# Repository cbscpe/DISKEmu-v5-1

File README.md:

# DISK Emulator

## Introduction
The Q-BUS is a bus invented by DEC and was first used for small PDP-11 systems like the LSI-11. There were several backplanes available from DEC
and 3rd parties. For a complete PDP-11 system you needed a CPU card, memory, at least a console and some sort of mass storage device. Depending
on the operation sytem you needed additional cards like a line time clock and others.

## Controller Card
This is a Q-BUS PCB for a Q-BUS PDP-11 system that emulates disk controllers depending on the firmware of the microcontroller and the CPLD design files.
Currently there are two disk controller emulation, a RLV12 controller with four RL01/02 disks attached and a MSCP controller with four units.
The Q-BUS controller provides a command line interface to control the functions and configuration and a SD-Card to store the PDP-11 disk images.

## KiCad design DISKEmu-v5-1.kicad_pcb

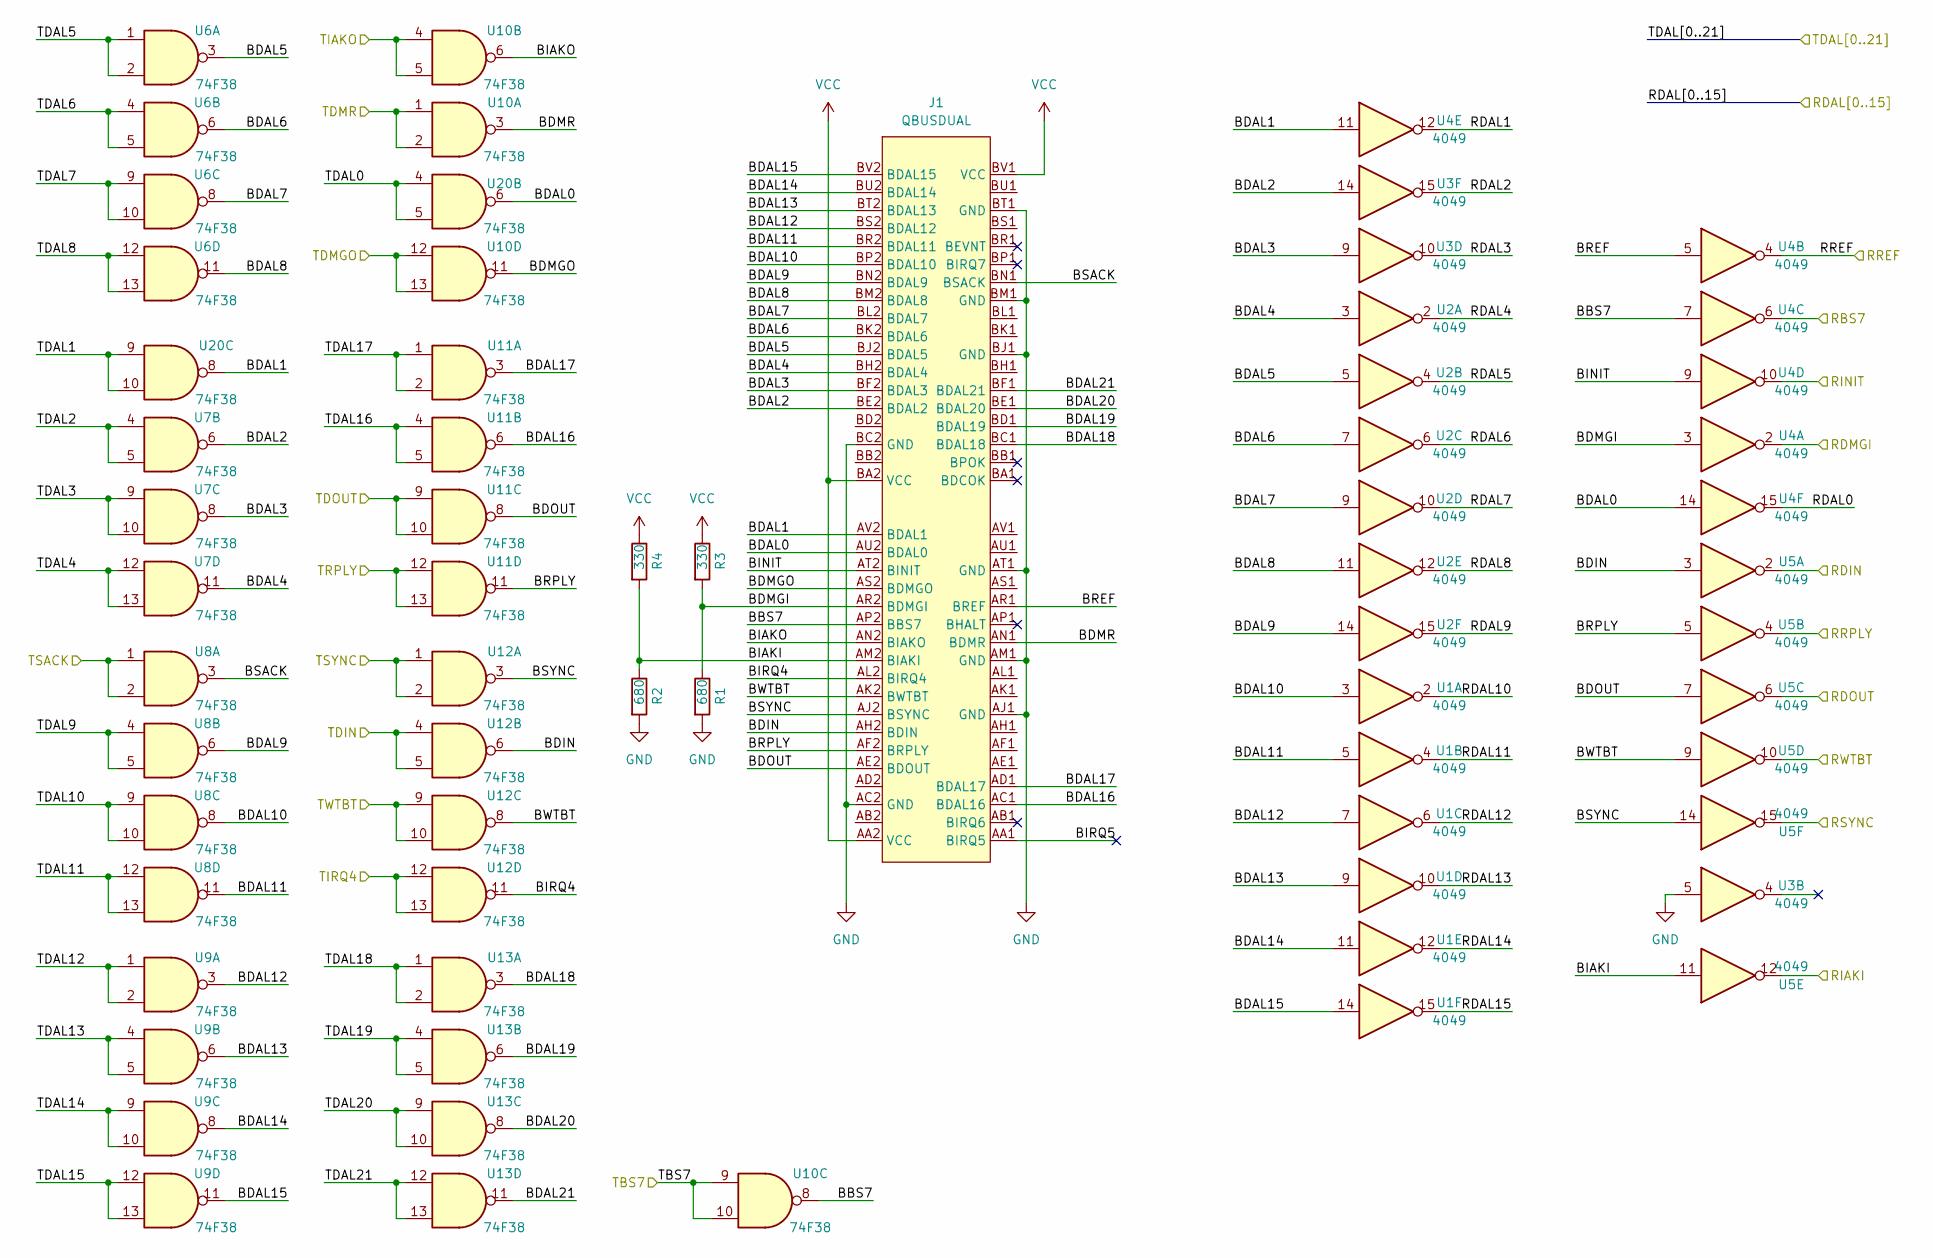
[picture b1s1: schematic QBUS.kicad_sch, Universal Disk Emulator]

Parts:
J1: QBUSDUAL; Q-Bus_Dual_Edge
R1, R2: 680; R_0603_1608Metric_Pad0.98x0.95mm_HandSolder
R3, R4: 330; R_0603_1608Metric_Pad0.98x0.95mm_HandSolder
U1, U2, U3, U4, U5: 4049; SOIC-16_3.9x9.9mm_P1.27mm
U6, U7, U8, U9, U10, U11, U12, U13, U20: 74F38; SOIC-14_3.9x8.7mm_P1.27mm

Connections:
/QBUS/BBS7: J1.AP2 (BBS7), U4.7, U10.8
/QBUS/BDAL0: J1.AU2 (BDAL0), U4.14, U20.6
/QBUS/BDAL1: J1.AV2 (BDAL1), U4.11, U20.8
/QBUS/BDAL2: J1.BE2 (BDAL2), U3.14, U7.6
/QBUS/BDAL3: J1.BF2 (BDAL3), U3.9, U7.8
/QBUS/BDAL4: J1.BH2 (BDAL4), U2.3, U7.11
/QBUS/BDAL5: J1.BJ2 (BDAL5), U2.5, U6.3
/QBUS/BDAL6: J1.BK2 (BDAL6), U2.7, U6.6
/QBUS/BDAL7: J1.BL2 (BDAL7), U2.9, U6.8
/QBUS/BDAL8: J1.BM2 (BDAL8), U2.11, U6.11
/QBUS/BDAL9: J1.BN2 (BDAL9), U2.14, U8.6
/QBUS/BDAL10: J1.BP2 (BDAL10), U1.3, U8.8
/QBUS/BDAL11: J1.BR2 (BDAL11), U1.5, U8.11
/QBUS/BDAL12: J1.BS2 (BDAL12), U1.7, U9.3
/QBUS/BDAL13: J1.BT2 (BDAL13), U1.9, U9.6
/QBUS/BDAL14: J1.BU2 (BDAL14), U1.11, U9.8
/QBUS/BDAL15: J1.BV2 (BDAL15), U1.14, U9.11
/QBUS/BDAL16: J1.AC1 (BDAL16), U11.6
/QBUS/BDAL17: J1.AD1 (BDAL17), U11.3
/QBUS/BDAL18: J1.BC1 (BDAL18), U13.3
/QBUS/BDAL19: J1.BD1 (BDAL19), U13.6
/QBUS/BDAL20: J1.BE1 (BDAL20), U13.8
/QBUS/BDAL21: J1.BF1 (BDAL21), U13.11
/QBUS/BDIN: J1.AH2 (BDIN), U5.3, U12.6
/QBUS/BDMGI: J1.AR2 (BDMGI), R1.1, R3.2, U4.3
/QBUS/BDMGO: J1.AS2 (BDMGO), U10.11
/QBUS/BDMR: J1.AN1 (BDMR), U10.3
/QBUS/BDOUT: J1.AE2 (BDOUT), U5.7, U11.8
/QBUS/BIAKI: J1.AM2 (BIAKI), R2.1, R4.2, U5.11
/QBUS/BIAKO: J1.AN2 (BIAKO), U10.6
/QBUS/BINIT: J1.AT2 (BINIT), U4.9
/QBUS/BIRQ4: J1.AL2 (BIRQ4), U12.11
/QBUS/BIRQ5: J1.AA1 (BIRQ5)
/QBUS/BREF: J1.AR1 (BREF), U4.5
/QBUS/BRPLY: J1.AF2 (BRPLY), U5.5, U11.11
/QBUS/BSACK: J1.BN1 (BSACK), U8.3
/QBUS/BSYNC: J1.AJ2 (BSYNC), U5.14, U12.3
/QBUS/BWTBT: J1.AK2 (BWTBT), U5.9, U12.8
/RBS7: U4.6; also elsewhere on the board
/RDAL0: U4.15; also elsewhere on the board
/RDAL1: U4.12; also elsewhere on the board
/RDAL2: U3.15; also elsewhere on the board
/RDAL3: U3.10; also elsewhere on the board
/RDAL4: U2.2; also elsewhere on the board
/RDAL5: U2.4; also elsewhere on the board
/RDAL6: U2.6; also elsewhere on the board
/RDAL7: U2.10; also elsewhere on the board
/RDAL8: U2.12; also elsewhere on the board
/RDAL9: U2.15; also elsewhere on the board
/RDAL10: U1.2; also elsewhere on the board
/RDAL11: U1.4; also elsewhere on the board
/RDAL12: U1.6; also elsewhere on the board
/RDAL13: U1.10; also elsewhere on the board
/RDAL14: U1.12; also elsewhere on the board
/RDAL15: U1.15; also elsewhere on the board
/RDIN: U5.2; also elsewhere on the board
/RDMIG: U4.2; also elsewhere on the board
/RDOUT: U5.6; also elsewhere on the board
/RIAKI: U5.12; also elsewhere on the board
/RINIT: U4.10; also elsewhere on the board
/RREF: U4.4; also elsewhere on the board
/RRPLY: U5.4; also elsewhere on the board
/RSYNC: U5.15; also elsewhere on the board
/RWTBT: U5.10; also elsewhere on the board
/TBS7: U10.9, U10.10; also elsewhere on the board
/TDAL0: U20.4, U20.5; also elsewhere on the board
/TDAL1: U20.9, U20.10; also elsewhere on the board
/TDAL2: U7.4, U7.5; also elsewhere on the board
/TDAL3: U7.9, U7.10; also elsewhere on the board
/TDAL4: U7.12, U7.13; also elsewhere on the board
/TDAL5: U6.1, U6.2; also elsewhere on the board
/TDAL6: U6.4, U6.5; also elsewhere on the board
/TDAL7: U6.9, U6.10; also elsewhere on the board
/TDAL8: U6.12, U6.13; also elsewhere on the board
/TDAL9: U8.4, U8.5; also elsewhere on the board
/TDAL10: U8.9, U8.10; also elsewhere on the board
/TDAL11: U8.12, U8.13; also elsewhere on the board
/TDAL12: U9.1, U9.2; also elsewhere on the board
/TDAL13: U9.4, U9.5; also elsewhere on the board
/TDAL14: U9.9, U9.10; also elsewhere on the board
/TDAL15: U9.12, U9.13; also elsewhere on the board
/TDAL16: U11.4, U11.5; also elsewhere on the board
/TDAL17: U11.1, U11.2; also elsewhere on the board
/TDAL18: U13.1, U13.2; also elsewhere on the board
/TDAL19: U13.4, U13.5; also elsewhere on the board
/TDAL20: U13.9, U13.10; also elsewhere on the board
/TDAL21: U13.12, U13.13; also elsewhere on the board
/TDIN: U12.4, U12.5; also elsewhere on the board
/TDMGO: U10.12, U10.13; also elsewhere on the board
/TDMR: U10.1, U10.2; also elsewhere on the board
/TDOUT: U11.9, U11.10; also elsewhere on the board
/TIAKO: U10.4, U10.5; also elsewhere on the board
/TIQR4: U12.12, U12.13; also elsewhere on the board
/TRPLY: U11.12, U11.13; also elsewhere on the board
/TSACK: U8.1, U8.2; also elsewhere on the board
/TSYNC: U12.1, U12.2; also elsewhere on the board
/TWTBT: U12.9, U12.10; also elsewhere on the board
GND: J1.AC2 (GND), J1.AJ1 (GND), J1.AM1 (GND), J1.AT1 (GND), J1.BC2 (GND), J1.BJ1 (GND), J1.BM1 (GND), J1.BT1 (GND), R1.2, R2.2, U3.5; also elsewhere on the board
VCC: J1.AA2 (VCC), J1.BA2 (VCC), J1.BV1 (VCC), R3.1, R4.1; also elsewhere on the board

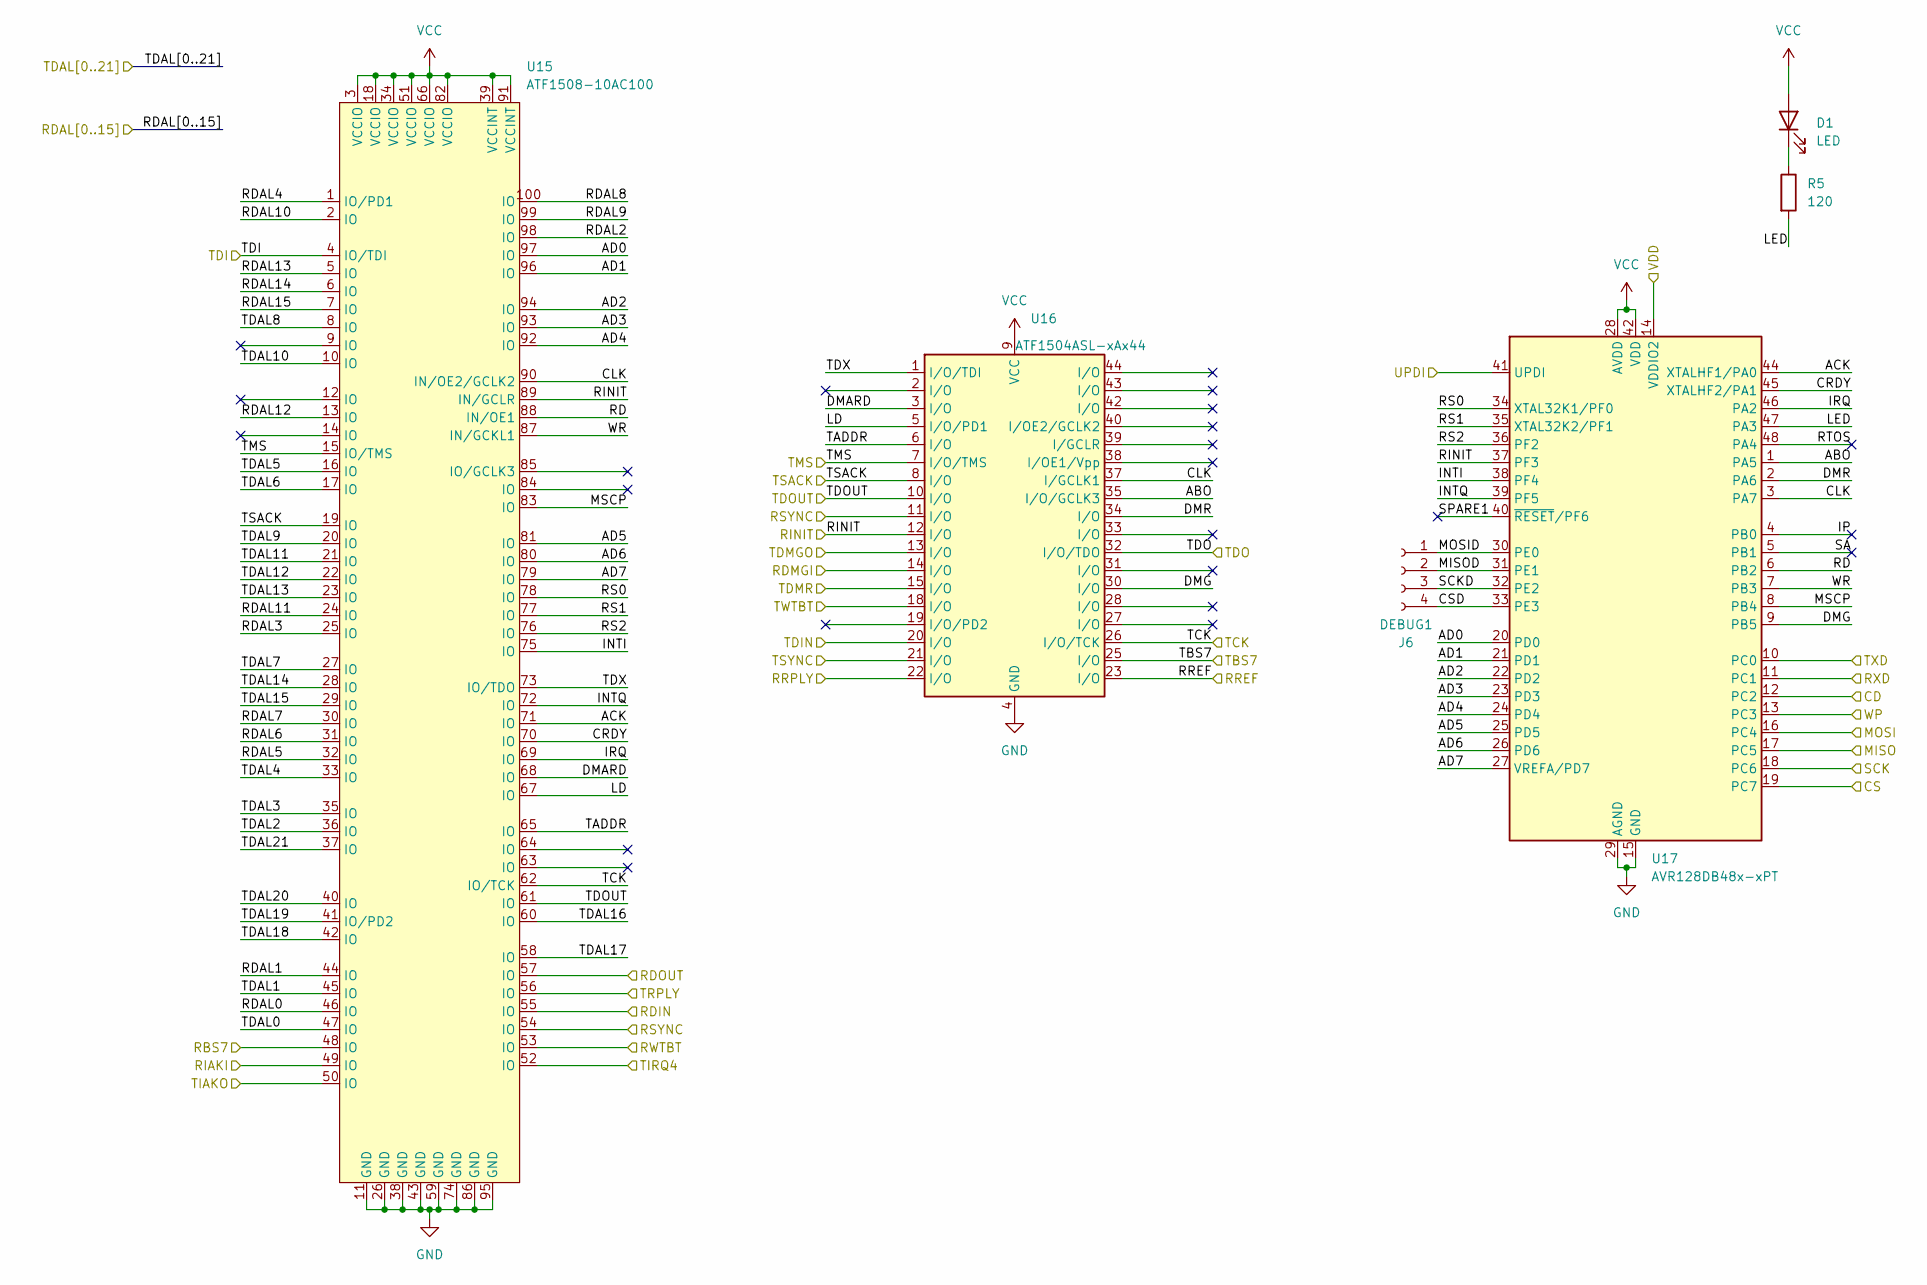
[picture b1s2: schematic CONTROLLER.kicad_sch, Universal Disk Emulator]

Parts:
D1: LED; LED_1206_3216Metric_Pad1.42x1.75mm_HandSolder
J6: DEBUG1; PinSocket_1x04_P2.54mm_Horizontal
R5: 120; R_0603_1608Metric_Pad0.98x0.95mm_HandSolder
U15: ATF1508-10AC100; TQFP-100_14x14mm_P0.5mm
U16: ATF1504ASL-xAx44; TQFP-44_10x10mm_P0.8mm
U17: AVR128DB48x-xPT; TQFP-48_7x7mm_P0.5mm

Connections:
/CD: U17.12 (PC2); also elsewhere on the board
/CONTROLLER/ABO: U16.35 (I/O/GCLK3), U17.1 (PA5)
/CONTROLLER/ACK: U15.71 (IO), U17.44 (XTALHF1/PA0)
/CONTROLLER/AD0: U15.97 (IO), U17.20 (PD0)
/CONTROLLER/AD1: U15.96 (IO), U17.21 (PD1)
/CONTROLLER/AD2: U15.94 (IO), U17.22 (PD2)
/CONTROLLER/AD3: U15.93 (IO), U17.23 (PD3)
/CONTROLLER/AD4: U15.92 (IO), U17.24 (PD4)
/CONTROLLER/AD5: U15.81 (IO), U17.25 (PD5)
/CONTROLLER/AD6: U15.80 (IO), U17.26 (PD6)
/CONTROLLER/AD7: U15.79 (IO), U17.27 (VREFA/PD7)
/CONTROLLER/CLK: U15.90 (IN/OE2/GCLK2), U16.37 (I/GCLK1), U17.3 (PA7)
/CONTROLLER/CRDY: U15.70 (IO), U17.45 (XTALHF2/PA1)
/CONTROLLER/CSD: J6.4, U17.33 (PE3)
/CONTROLLER/DMARD: U15.68 (IO), U16.3 (I/O)
/CONTROLLER/DMG: U16.30 (I/O), U17.9 (PB5)
/CONTROLLER/DMR: U16.34 (I/O), U17.2 (PA6)
/CONTROLLER/INTI: U15.75 (IO), U17.38 (PF4)
/CONTROLLER/INTQ: U15.72 (IO), U17.39 (PF5)
/CONTROLLER/IP: U17.4 (PB0)
/CONTROLLER/IRQ: U15.69 (IO), U17.46 (PA2)
/CONTROLLER/LD: U15.67 (IO), U16.5 (I/O/PD1)
/CONTROLLER/LED: R5.2, U17.47 (PA3)
/CONTROLLER/MISOD: J6.2, U17.31 (PE1)
/CONTROLLER/MOSID: J6.1, U17.30 (PE0)
/CONTROLLER/MSCP: U15.83 (IO), U17.8 (PB4)
/CONTROLLER/RD: U15.88 (IN/OE1), U17.6 (PB2)
/CONTROLLER/RS0: U15.78 (IO), U17.34 (XTAL32K1/PF0)
/CONTROLLER/RS1: U15.77 (IO), U17.35 (XTAL32K2/PF1)
/CONTROLLER/RS2: U15.76 (IO), U17.36 (PF2)
/CONTROLLER/RTOS: U17.48 (PA4)
/CONTROLLER/SA: U17.5 (PB1)
/CONTROLLER/SCKD: J6.3, U17.32 (PE2)
/CONTROLLER/SPARE1: U17.40 (~RESET/PF6)
/CONTROLLER/TADDR: U15.65 (IO), U16.6 (I/O)
/CONTROLLER/TDX: U15.73 (IO/TDO), U16.1 (I/O/TDI)
/CONTROLLER/WR: U15.87 (IN/GCKL1), U17.7 (PB3)
/CS: U17.19 (PC7); also elsewhere on the board
/MISO: U17.17 (PC5); also elsewhere on the board
/MOSI: U17.16 (PC4); also elsewhere on the board
/RBS7: U15.48 (IO); also elsewhere on the board
/RDAL0: U15.46 (IO); also elsewhere on the board
/RDAL1: U15.44 (IO); also elsewhere on the board
/RDAL2: U15.98 (IO); also elsewhere on the board
/RDAL3: U15.25 (IO); also elsewhere on the board
/RDAL4: U15.1 (IO/PD1); also elsewhere on the board
/RDAL5: U15.32 (IO); also elsewhere on the board
/RDAL6: U15.31 (IO); also elsewhere on the board
/RDAL7: U15.30 (IO); also elsewhere on the board
/RDAL8: U15.100 (IO); also elsewhere on the board
/RDAL9: U15.99 (IO); also elsewhere on the board
/RDAL10: U15.2 (IO); also elsewhere on the board
/RDAL11: U15.24 (IO); also elsewhere on the board
/RDAL12: U15.13 (IO); also elsewhere on the board
/RDAL13: U15.5 (IO); also elsewhere on the board
/RDAL14: U15.6 (IO); also elsewhere on the board
/RDAL15: U15.7 (IO); also elsewhere on the board
/RDIN: U15.55 (IO); also elsewhere on the board
/RDMIG: U16.14 (I/O); also elsewhere on the board
/RDOUT: U15.57 (IO); also elsewhere on the board
/RIAKI: U15.49 (IO); also elsewhere on the board
/RINIT: U15.89 (IN/GCLR), U16.12 (I/O), U17.37 (PF3); also elsewhere on the board
/RREF: U16.23 (I/O); also elsewhere on the board
/RRPLY: U16.22 (I/O); also elsewhere on the board
/RSYNC: U15.54 (IO), U16.11 (I/O); also elsewhere on the board
/RWTBT: U15.53 (IO); also elsewhere on the board
/RXD: U17.11 (PC1); also elsewhere on the board
/SCK: U17.18 (PC6); also elsewhere on the board
/TBS7: U16.25 (I/O); also elsewhere on the board
/TCK: U15.62 (IO/TCK), U16.26 (I/O/TCK); also elsewhere on the board
/TDAL0: U15.47 (IO); also elsewhere on the board
/TDAL1: U15.45 (IO); also elsewhere on the board
/TDAL2: U15.36 (IO); also elsewhere on the board
/TDAL3: U15.35 (IO); also elsewhere on the board
/TDAL4: U15.33 (IO); also elsewhere on the board
/TDAL5: U15.16 (IO); also elsewhere on the board
/TDAL6: U15.17 (IO); also elsewhere on the board
/TDAL7: U15.27 (IO); also elsewhere on the board
/TDAL8: U15.8 (IO); also elsewhere on the board
/TDAL9: U15.20 (IO); also elsewhere on the board
/TDAL10: U15.10 (IO); also elsewhere on the board
/TDAL11: U15.21 (IO); also elsewhere on the board
/TDAL12: U15.22 (IO); also elsewhere on the board
/TDAL13: U15.23 (IO); also elsewhere on the board
/TDAL14: U15.28 (IO); also elsewhere on the board
/TDAL15: U15.29 (IO); also elsewhere on the board
/TDAL16: U15.60 (IO); also elsewhere on the board
/TDAL17: U15.58 (IO); also elsewhere on the board
/TDAL18: U15.42 (IO); also elsewhere on the board
/TDAL19: U15.41 (IO/PD2); also elsewhere on the board
/TDAL20: U15.40 (IO); also elsewhere on the board
/TDAL21: U15.37 (IO); also elsewhere on the board
/TDI: U15.4 (IO/TDI); also elsewhere on the board
/TDIN: U16.20 (I/O); also elsewhere on the board
/TDMGO: U16.13 (I/O); also elsewhere on the board
/TDMR: U16.15 (I/O); also elsewhere on the board
/TDO: U16.32 (I/O/TDO); also elsewhere on the board
/TDOUT: U15.61 (IO), U16.10 (I/O); also elsewhere on the board
/TIAKO: U15.50 (IO); also elsewhere on the board
/TIQR4: U15.52 (IO); also elsewhere on the board
/TMS: U15.15 (IO/TMS), U16.7 (I/O/TMS); also elsewhere on the board
/TRPLY: U15.56 (IO); also elsewhere on the board
/TSACK: U15.19 (IO), U16.8 (I/O); also elsewhere on the board
/TSYNC: U16.21 (I/O); also elsewhere on the board
/TWTBT: U16.18 (I/O); also elsewhere on the board
/TXD: U17.10 (PC0); also elsewhere on the board
/UPDI: U17.41 (UPDI); also elsewhere on the board
/VDD: U17.14 (VDDIO2); also elsewhere on the board
/WP: U17.13 (PC3); also elsewhere on the board
GND: U15.11 (GND), U15.26 (GND), U15.38 (GND), U15.43 (GND), U15.59 (GND), U15.74 (GND), U15.86 (GND), U15.95 (GND), U16.4 (GND), U16.16 (GND), U16.24 (GND), U16.36 (GND), U17.15 (GND), U17.29 (AGND), U17.43 (GND); also elsewhere on the board
unnamed: D1.1 (K), R5.1
VCC: D1.2 (A), U15.3 (VCCIO), U15.18 (VCCIO), U15.34 (VCCIO), U15.39 (VCCINT), U15.51 (VCCIO), U15.66 (VCCIO), U15.82 (VCCIO), U15.91 (VCCINT), U16.9 (VCC), U16.17 (VCC), U16.29 (VCC), U16.41 (VCC), U17.28 (AVDD), U17.42 (VDD); also elsewhere on the board

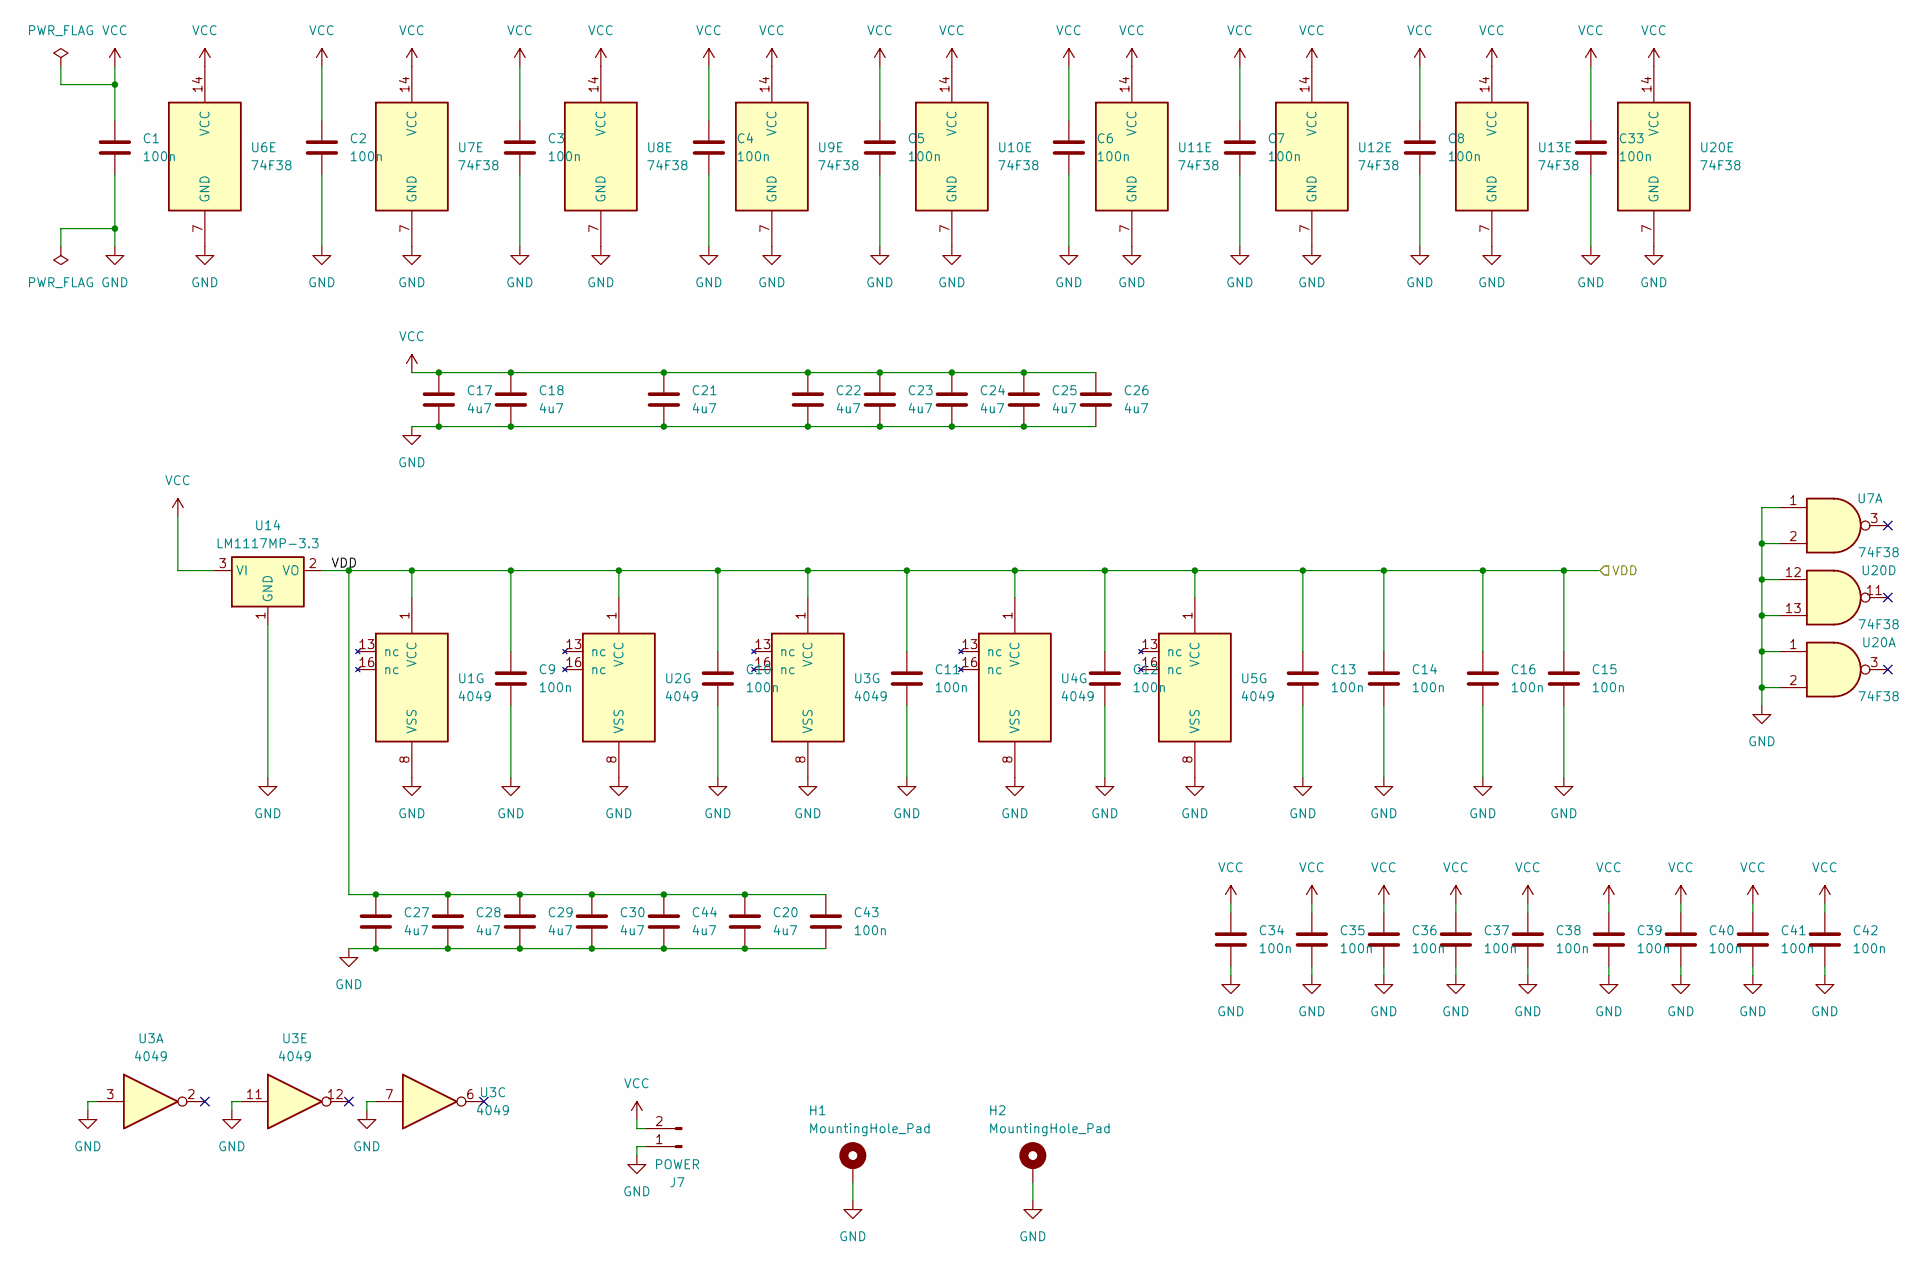
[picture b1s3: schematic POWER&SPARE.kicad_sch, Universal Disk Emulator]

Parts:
C1, C2, C3, C4, C5, C6, C7, C8, C9, C10, C11, C12, C13, C14, C15, C16, C33, C34, C35, C36, C37, C38, C39, C40, C41, C42, C43: 100n; C_0603_1608Metric_Pad1.08x0.95mm_HandSolder
C17, C18, C20, C21, C22, C23, C24, C25, C26, C27, C28, C29, C30, C44: 4u7; CP_EIA-3528-12_Kemet-T_HandSolder
H1, H2: MountingHole_Pad; MountingHole_3.2mm_M3_DIN965_Pad
J7: POWER; PinHeader_1x02_P2.54mm_Horizontal
U1, U2, U3, U4, U5: 4049; SOIC-16_3.9x9.9mm_P1.27mm
U6, U7, U8, U9, U10, U11, U12, U13, U20: 74F38; SOIC-14_3.9x8.7mm_P1.27mm
U14: LM1117MP-3.3; SOT-223-3_TabPin2

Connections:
/VDD: C9.1, C10.1, C11.1, C12.1, C13.1, C14.1, C15.1, C16.1, C20.1, C27.1, C28.1, C29.1, C30.1, C43.1, C44.1, U1.1 (VCC), U2.1 (VCC), U3.1 (VCC), U4.1 (VCC), U5.1 (VCC), U14.2 (VO); also elsewhere on the board
GND: C1.2, C2.2, C3.2, C4.2, C5.2, C6.2, C7.2, C8.2, C9.2, C10.2, C11.2, C12.2, C13.2, C14.2, C15.2, C16.2, C17.2, C18.2, C20.2, C21.2, C22.2, C23.2, C24.2, C25.2, C26.2, C27.2, C28.2, C29.2, C30.2, C33.2, C34.2, C35.2, C36.2, C37.2, C38.2, C39.2, C40.2, C41.2, C42.2, C43.2, C44.2, H1.1 (1_1), H2.1 (1_1), J7.1, U1.8 (VSS), U2.8 (VSS), U3.3, U3.7, U3.8 (VSS), U3.11, U4.8 (VSS), U5.8 (VSS), U6.7 (GND), U7.1, U7.2, U7.7 (GND), U8.7 (GND), U9.7 (GND), U10.7 (GND), U11.7 (GND), U12.7 (GND), U13.7 (GND), U14.1 (GND), U20.1, U20.2, U20.7 (GND), U20.12, U20.13; also elsewhere on the board
VCC: C1.1, C2.1, C3.1, C4.1, C5.1, C6.1, C7.1, C8.1, C17.1, C18.1, C21.1, C22.1, C23.1, C24.1, C25.1, C26.1, C33.1, C34.1, C35.1, C36.1, C37.1, C38.1, C39.1, C40.1, C41.1, C42.1, J7.2, U6.14 (VCC), U7.14 (VCC), U8.14 (VCC), U9.14 (VCC), U10.14 (VCC), U11.14 (VCC), U12.14 (VCC), U13.14 (VCC), U14.3 (VI), U20.14 (VCC); also elsewhere on the board

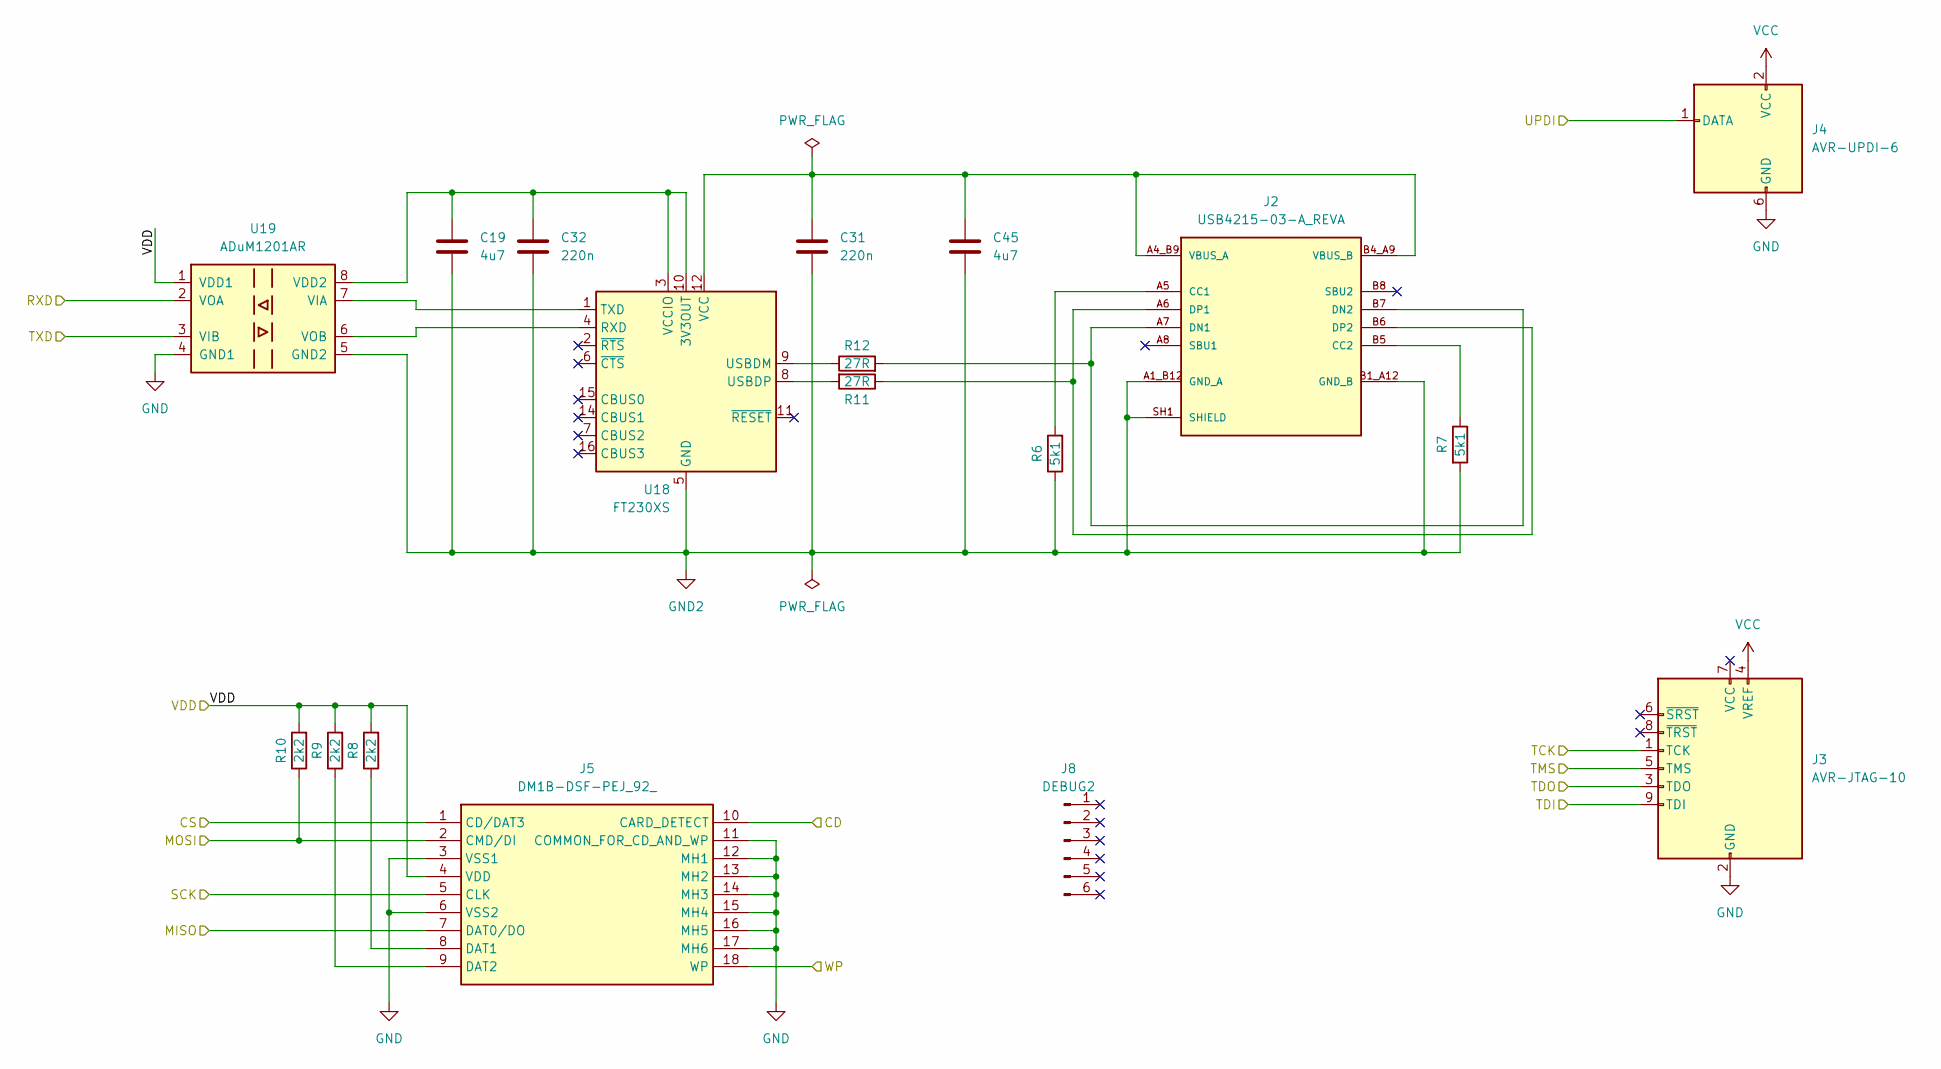
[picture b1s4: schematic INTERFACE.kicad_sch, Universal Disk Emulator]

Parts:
C19, C45: 4u7; CP_EIA-3528-12_Kemet-T_HandSolder
C31, C32: 220n; C_0603_1608Metric_Pad1.08x0.95mm_HandSolder
J2: USB4215-03-A_REVA; GCT_USB4215-03-A-REVB
J3: AVR-JTAG-10; IDC-Header_2x05_P2.54mm_Horizontal
J4: AVR-UPDI-6; IDC-Header_2x03_P2.54mm_Horizontal
J5: DM1B-DSF-PEJ_92_; DM1B-DSF-PEJ92; Mouser Part Number 798-DM1BDSFPEJ92
J8: DEBUG2; PinHeader_1x06_P2.54mm_Vertical
R6, R7: 5k1; R_0603_1608Metric_Pad0.98x0.95mm_HandSolder
R8, R9, R10: 2k2; R_0603_1608Metric_Pad0.98x0.95mm_HandSolder
R11, R12: 27R; R_0603_1608Metric_Pad0.98x0.95mm_HandSolder
U18: FT230XS; SSOP-16_3.9x4.9mm_P0.635mm
U19: ADuM1201AR; SOIC-8_3.9x4.9mm_P1.27mm

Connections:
/CD: J5.10 (CARD_DETECT); also elsewhere on the board
/CS: J5.1 (CD/DAT3); also elsewhere on the board
/MISO: J5.7 (DAT0/DO); also elsewhere on the board
/MOSI: J5.2 (CMD/DI), R10.1; also elsewhere on the board
/RXD: U19.2 (VOA); also elsewhere on the board
/SCK: J5.5 (CLK); also elsewhere on the board
/TCK: J3.1 (TCK); also elsewhere on the board
/TDI: J3.9 (TDI); also elsewhere on the board
/TDO: J3.3 (TDO); also elsewhere on the board
/TMS: J3.5 (TMS); also elsewhere on the board
/TXD: U19.3 (VIB); also elsewhere on the board
/UPDI: J4.1 (DATA); also elsewhere on the board
/VDD: J5.4 (VDD), R8.2, R9.2, R10.2, U19.1 (VDD1); also elsewhere on the board
/WP: J5.18 (WP); also elsewhere on the board
GND: J3.2 (GND), J3.10 (GND), J4.6 (GND), J5.3 (VSS1), J5.6 (VSS2), J5.11 (COMMON_FOR_CD_AND_WP), J5.12 (MH1), J5.13 (MH2), J5.14 (MH3), J5.15 (MH4), J5.16 (MH5), J5.17 (MH6), U19.4 (GND1); also elsewhere on the board
GND2: C19.2, C31.2, C32.2, C45.2, J2.A1_B12 (GND_A), J2.B1_A12 (GND_B), J2.SH1 (SHIELD), J2.SH2 (SHIELD), J2.SH3 (SHIELD), J2.SH4 (SHIELD), R6.1, R7.2, U18.5 (GND), U18.13 (GND), U19.5 (GND2)
unnamed: J2.A5 (CC1), R6.2
unnamed: J2.B5 (CC2), R7.1
unnamed: J2.A7 (DN1), J2.B7 (DN2), R12.2
unnamed: J2.A6 (DP1), J2.B6 (DP2), R11.1
unnamed: C31.1, C45.1, J2.A4_B9 (VBUS_A), J2.B4_A9 (VBUS_B), U18.12 (VCC)
unnamed: J5.8 (DAT1), R8.1
unnamed: J5.9 (DAT2), R9.1
unnamed: C19.1, C32.1, U18.3 (VCCIO), U18.10 (3V3OUT), U19.8 (VDD2)
unnamed: U18.4 (RXD), U19.6 (VOB)
unnamed: U18.1 (TXD), U19.7 (VIA)
unnamed: R12.1, U18.9 (USBDM)
unnamed: R11.2, U18.8 (USBDP)
VCC: J3.4 (VREF), J4.2 (VCC); also elsewhere on the board

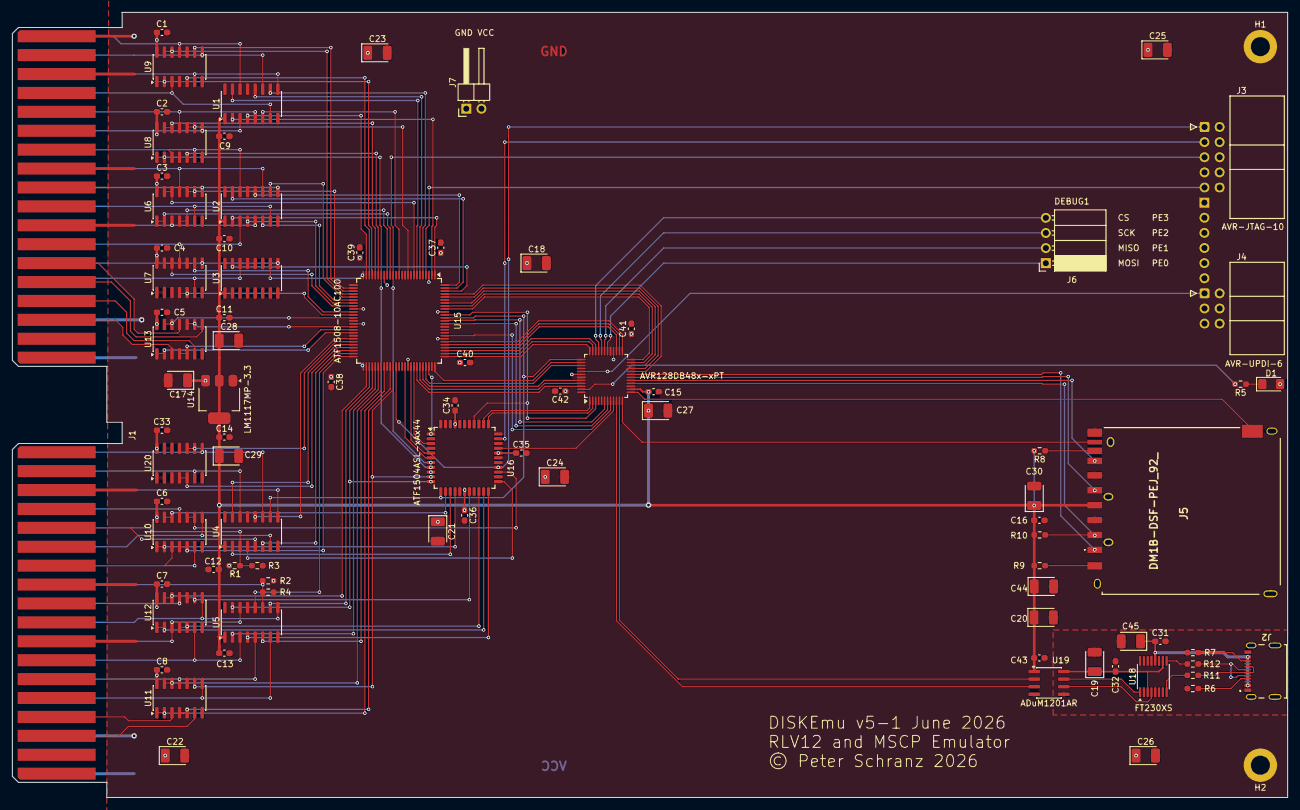
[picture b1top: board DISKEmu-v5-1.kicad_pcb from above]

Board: 2 copper layers, 214.1 x 131.8 mm, 88 parts (1 on the bottom side), 158 nets.

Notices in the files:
DISKEmu-v5-1.kicad_pcb:
© Peter Schranz 2026
